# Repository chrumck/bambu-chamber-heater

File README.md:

# Bambu Lab X1 Chamber Heater Controller

## Description

Code for Bambu Lab X1 Carbon chamber heater controller.
It controls the chamber heater fan, heater core, the chamber light, and the external enclosure fan.
The input are two temperature sensors, the chamber temp sensor and the heater core temp sensor.

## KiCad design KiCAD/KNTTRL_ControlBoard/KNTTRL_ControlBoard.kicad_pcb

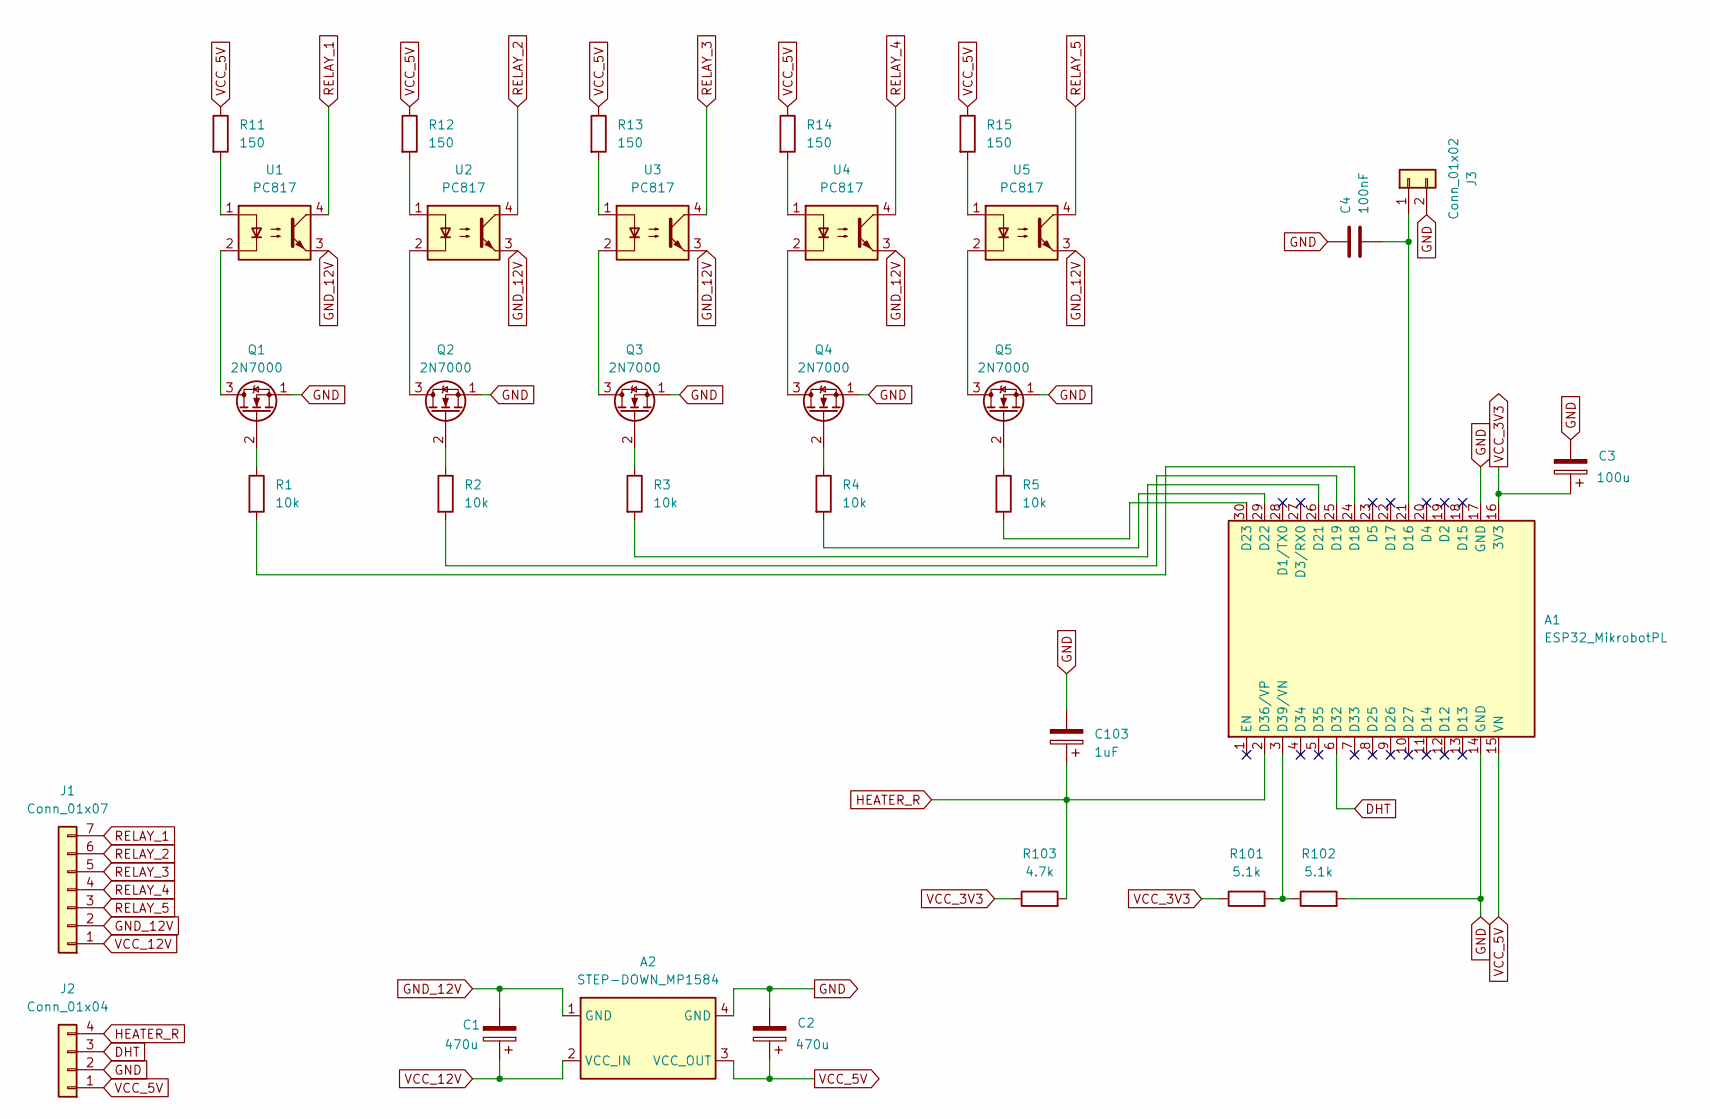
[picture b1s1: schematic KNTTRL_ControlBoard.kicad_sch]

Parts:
A1: ESP32_MikrobotPL
A2: STEP-DOWN_MP1584
C1, C2: 470u; CP_Radial_D5.0mm_P2.50mm
C3: 100u; CP_Radial_D5.0mm_P2.50mm
C4: 100nF; C_Disc_D5.0mm_W2.5mm_P2.50mm
C103: 1uF; CP_Radial_D5.0mm_P2.50mm
J1: Conn_01x07; PinHeader_1x07_P2.54mm_Vertical
J2: Conn_01x04; PinHeader_1x04_P2.54mm_Vertical
J3: Conn_01x02; PinHeader_1x02_P2.54mm_Vertical
Q1, Q2, Q3, Q4, Q5: 2N7000; TO-92_Inline_Wide
R1, R2, R3, R4, R5: 10k; R_Axial_DIN0207_L6.3mm_D2.5mm_P7.62mm_Horizontal
R11, R12, R13, R14, R15: 150; R_Axial_DIN0309_L9.0mm_D3.2mm_P2.54mm_Vertical
R101, R102: 5.1k; R_Axial_DIN0207_L6.3mm_D2.5mm_P7.62mm_Horizontal
R103: 4.7k; R_Axial_DIN0207_L6.3mm_D2.5mm_P7.62mm_Horizontal
U1, U2, U3, U4, U5: PC817; DIP-4_W7.62mm

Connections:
DHT: A1.6 (D32), J2.3
GND: A1.14 (GND), A1.17 (GND), A2.4 (GND), C2.2, C3.2, C4.1, C103.2, J2.2, J3.2, Q1.1 (S), Q2.1 (S), Q3.1 (S), Q4.1 (S), Q5.1 (S), R102.2
GND_12V: A2.1 (GND), C1.2, J1.2 (GND_12V), U1.3, U2.3, U3.3, U4.3, U5.3
HEATER_R: A1.2 (D36/VP), C103.1, J2.4, R103.2
unnamed: A1.21 (D16), C4.2, J3.1
unnamed: A1.24 (D18), R1.2
unnamed: A1.25 (D19), R2.2
unnamed: A1.26 (D21), R3.2
unnamed: A1.29 (D22), R4.2
unnamed: A1.30 (D23), R5.2
unnamed: A1.3 (D39/VN), R101.2, R102.1
unnamed: Q1.3 (D), U1.2
unnamed: Q1.2 (G), R1.1
unnamed: Q2.3 (D), U2.2
unnamed: Q2.2 (G), R2.1
unnamed: Q3.3 (D), U3.2
unnamed: Q3.2 (G), R3.1
unnamed: Q4.3 (D), U4.2
unnamed: Q4.2 (G), R4.1
unnamed: Q5.3 (D), U5.2
unnamed: Q5.2 (G), R5.1
unnamed: R11.2, U1.1
unnamed: R12.2, U2.1
unnamed: R13.2, U3.1
unnamed: R14.2, U4.1
unnamed: R15.2, U5.1
RELAY_1: J1.7, U1.4
RELAY_2: J1.6, U2.4
RELAY_3: J1.5, U3.4
RELAY_4: J1.4, U4.4
RELAY_5: J1.3, U5.4
VCC_3V3: A1.16 (3V3), C3.1, R101.1, R103.1
VCC_5V: A1.15 (VN), A2.3 (VCC_OUT), C2.1, J2.1, R11.1, R12.1, R13.1, R14.1, R15.1
VCC_12V: A2.2 (VCC_IN), C1.1, J1.1 (VCC_12V)

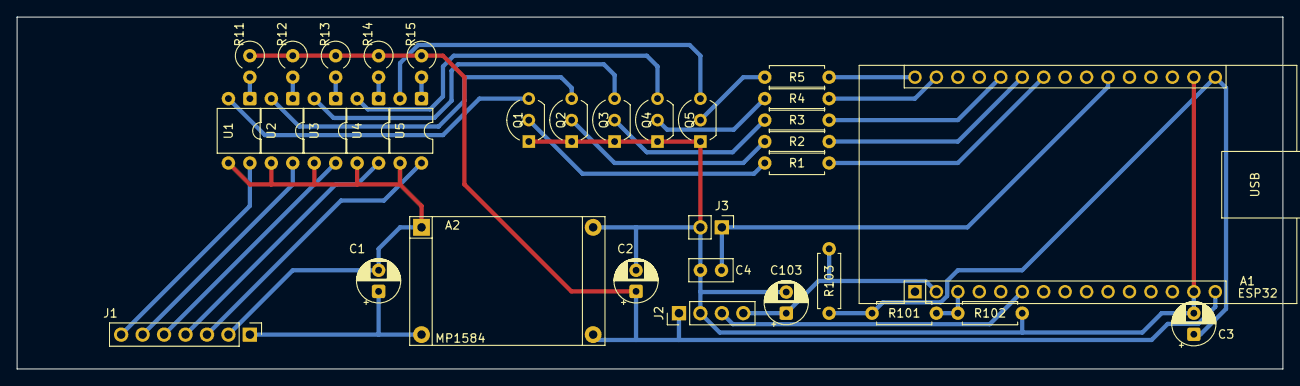
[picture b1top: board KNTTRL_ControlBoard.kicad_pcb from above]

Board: 2 copper layers, 149.9 x 41.7 mm, 33 parts (0 on the bottom side), 34 nets.

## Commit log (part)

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2024-02-15 Add max time of 12 hours, shorten loop to 2.5s, allow for 1 dht fail without switching the heater off
2024-02-15 Add serial commands
2024-02-16 lower heater temps to max 140 degC
2024-02-16 tweak heater on/off temps; print vref
2024-02-20 move files to 'design' folder
2024-02-20 minor cleanup
2024-02-20 bump heater core temps to 110/95; add duty cycle
2024-02-20 make time setting count from moment of setting
2024-02-20 add request to show time and temp
2024-02-21 tweak temperatures
2024-06-22 bump temps and lower default on time
2024-06-28 bump heater temp to 125 degC; tweak serial reporting
2024-06-29 tweak reporting format
2024-06-29 minor tweak
2024-07-01 minor tweaks in reporting
2024-07-20 bump max allowed DHT fail count to 5
2025-05-28 convert to ESP32, set up arduino IDE
2025-05-28 Add svelte kit
2025-05-28 regenerate svelte scaffolding, no tailwind
2025-05-29 Set up for static inline html
2025-05-29 change favicon
2025-05-30 Try add manifest
2025-05-30 work on manifest
2025-05-30 tweaking icons
2025-05-30 upgrade to yarn 4.9.1
2025-06-01 more work on manifest and favicon
2025-06-01 more work on manifest
2025-06-01 add prettier config
2025-06-01 try use onMount from svelte
2025-06-01 final take on favicon and manifest
2025-06-01 move HTML head manipulation to layout.svelte
2025-06-02 start working on websocket
2025-06-02 minor updates to packages
2025-06-02 use attachments for icon and manifest
2025-06-02 fix prettierrc config
2025-06-12 add ntc spec sheet
2025-06-12 add websocket logic
2025-06-12 fix web socket url
2025-06-12 start working on main page layout
2025-06-15 move css to layout.css
2025-06-15 add switches
2025-06-15 Add main app label
2025-06-16 updates to css
2025-06-16 move switch to a component; add header 3d printer icon
2025-06-16 move header to separate component
2025-06-16 convert build to full SPA to prevent duplicates in html
2025-06-16 more html and css
2025-06-17 Refactoring and tweaks
2025-06-17 minor tweaks to gauge
2025-06-17 add request codes
2025-06-17 first stab at a popup component
2025-06-17 more work on Popup
2025-06-17 Finished popup
2025-06-17 add scratchpad folder
2025-06-17 minor updates
2025-06-17 tweaks to websocket
2025-06-17 minor tweaks
2025-06-18 Add 'connecting' overlay
2025-06-18 minor refactor
2025-06-19 refactor ino for compiling on esp32
2025-06-19 rename ino file to KnurToryTroller
2025-06-19 rename ino back, Arduino IDE complaining
2025-06-19 make use of Preferences.h
2025-06-19 add wifi init
2025-06-20 first round of refactoring ino for websocket and more relays
2025-06-20 finish refactoring code for all fans and stuff
2025-06-21 add println where necessary
2025-06-21 more work done on websocket
2025-06-21 remove arduino extension; prep for platformio
2025-06-21 move fronted source files to src_front
2025-06-21 add platformio project files
2025-06-21 remove ignored files
2025-06-21 try move arduino code to main.cpp
2025-06-21 move code out of bambu-chamber-heater.ino
2025-06-21 minor tweak in gitignore
2025-06-21 fix pin assignment and serial baud rate
2025-06-21 Add data broadcasting to esp code
2025-06-21 fix svelte setup for ts defs
2025-06-21 Add first webSocket reads; Fix rendering invalid values in Gauge.svelte
2025-06-21 Wire up websocket messages to page state
2025-06-21 wire up ws requests
2025-06-21 tweaks to websocket error handling
2025-06-21 more tweaks to ws error handling
2025-06-21 rewrite socket error handling
2025-06-21 minor fixes
2025-06-22 switch to using analogReadMillivolts
2025-06-22 calibrate ADC
2025-06-22 fix relay control for n-mos drivers
2025-06-22 change heater V to 3.3V
2025-06-22 update design files
2025-06-22 file renames
2025-06-23 Add handling of light button press
2025-06-23 Finish deploying html to esp32
2025-06-23 shuffle pin assignments
2025-06-24 add door fan on on temp 1 deg above set
2025-06-26 update pin assignments
2025-06-26 refactor ADC reading logic
2025-06-26 reassign light button
2025-06-26 set default temp to 60 degC
2025-06-26 fix door and aux fan logic
2025-06-26 fix heater logic. other tweaks
2025-06-26 html fixes
2025-06-26 remove calls to serial in interrupts, possibly clashing with main code trying to print to serial at the same time
2025-06-28 remove switch interrupt handler, replace with polling
2025-06-28 add reset_reason to serial commands
2025-07-09 refactor to use platformIO; bump DHT retry to 8
2025-07-13 minor renames
2025-07-13 Add KiCAD design for KNTTRL_ControlBoard
2025-07-13 minor tweaks to ADC constants
2025-07-20 update gitignore for KiCad lock files
2025-07-20 assign pins 18~23 to as relay output
2025-07-29 fix pin assignments
2025-07-29 update KiCAD files
2025-07-29 decrease adc max fails to 3
2025-08-01 update code to switch off chamber cooling after time elapses
2025-08-25 Svelte: make popup focus on input when opened
2025-08-25 increase door fan hysteresis
2025-08-26 make popup select all
